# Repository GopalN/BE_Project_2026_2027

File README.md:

# BE CAPSTONE PROJECT 

## 🤖 Decentralized Swarm Autonomous Ground Vehicles
<p align="left">
  
</p>

---
## 👥 Team Details

| **Sr. No.** | **Name of Student** | **Roll No.** | **Branch** | **Email ID** |
|:---:|:---|:---:|:---|:---|
| 1 | Abbas Najam | 59 |Automation and Robotics | [2023.abbas.najam@ves.ac.in](mailto:2023.abbas.najam@ves.ac.in) |
| 2 | Mayuresh Joshi | 49 | Automation and Robotics | [2023.mayuresh.joshi@ves.ac.in](mailto:2023.mayuresh.joshi@ves.ac.in) |
| 3 | Shravan Umrale | 66 | Automation and Robotics | [2023.shravan.umrale@ves.ac.in](mailto:2023.shravan.umrale@ves.ac.in) |
| 4 | Yash Vaychal | 31 | Automation and Robotics | [2023.yash.vaychal@ves.ac.in](mailto:2023.yash.vaychal@ves.ac.in) |

---

## Guide Details

**Project Guide:**  Deepti Khimani

**Department:** Automation and Robotics  

**Institute:** VESIT, Mumbai

# 📌 Project Overview

Swarm robotics is inspired by the collective behavior observed in nature such as ants, bees, and birds. It involves multiple autonomous robots coordinating with each other to accomplish complex tasks efficiently.

This project focuses on developing a **decentralized swarm of Autonomous Ground Vehicles (AGVs)** capable of collaborative operation without depending on a single central controller.

The proposed system combines autonomous navigation, mapping, localization, swarm intelligence, distributed decision-making, communication, and fault detection and recovery.

The system is designed to operate reliably even when an individual robot experiences a failure.

### Key Capabilities

* 🤖 Autonomous navigation
* 🗺️ Mapping and localization
* 📡 Robot-to-robot communication
* 🧠 Decentralized decision-making
* 🤝 Swarm intelligence
* 🚨 Fault detection
* 🔄 Fault recovery
* 🧭 Path planning
* 🚧 Obstacle avoidance
* 🔀 Task reallocation
* ⚙️ Distributed motion control

---

# 🎯 Problem Statement

Most swarm robotic systems currently exist in a **centralized architecture**, where a central controller is responsible for coordinating the robots.

However, in real-world applications, we cannot rely on a single point of failure. If the central controller fails or communication with it is lost, the entire swarm can be affected.

Therefore, this project aims to develop a **decentralized swarm system with fault detection and recovery mechanisms**, where individual robots can communicate with neighboring robots, make local decisions, detect failures, and continue the mission collectively.

---

# 🚀 Objectives

The major objectives of this project are:

* Develop a decentralized multi-robot swarm system.
* Enable communication between multiple autonomous ground vehicles.
* Implement autonomous navigation.
* Implement mapping and localization.
* Develop obstacle avoidance capabilities.
* Implement distributed decision-making.
* Introduce swarm intelligence algorithms.
* Detect communication, sensor, and motor-related faults.
* Develop fault recovery mechanisms.
* Reallocate tasks when a robot becomes unavailable.
* Maintain swarm operation after individual robot failure.
* Validate the system through simulation.
* Develop and test physical AGV prototypes.
* Evaluate swarm performance under different fault conditions.

---
## Existing System

Describe the currently available system or method.

Mention its limitations:

- High cost
- Low accuracy
- Manual process
- Lack of automation
- Poor scalability
- Limited accessibility

---

## Proposed System

Describe your proposed solution.

Include:

- Main idea
- How it works
- Major components
- Expected benefits

---

## System Architecture

Add block diagram or system architecture image here.

```markdown

````

Briefly explain the architecture.

---

## Hardware Requirements

| Sr. No. | Component | Specification | Quantity | Purpose |
| ------- | --------- | ------------- | -------- | ------- |
| 1       |           |               |          |         |
| 2       |           |               |          |         |
| 3       |           |               |          |         |
| 4       |           |               |          |         |

---

## Software Requirements

| Sr. No. | Software / Tool | Version | Purpose |
| ------- | --------------- | ------- | ------- |
| 1       |                 |         |         |
| 2       |                 |         |         |
| 3       |                 |         |         |

---

## Technologies Used

Mention technologies used in the project.

Example:

* Embedded C / Python / JavaScript
* Arduino / STM32 / ESP32 / Raspberry Pi
* ROS / MATLAB / Simulink
* Machine Learning / Computer Vision
* IoT / Cloud / Mobile App
* PCB Design / CAD Design

---

## Methodology

Explain the step-by-step approach.

1. Literature survey
2. Problem identification
3. Requirement analysis
4. System design
5. Hardware/software development
6. Integration
7. Testing and validation
8. Documentation and publication

---

## Project Timeline

| Week / Month | Task Planned          | Status                            |
| ------------ | --------------------- | --------------------------------- |
| Week 1       | Problem finalization  | Pending / In Progress / Completed |
| Week 2       | Literature survey     |                                   |
| Week 3       | Requirement analysis  |                                   |
| Week 4       | System design         |                                   |
| Week 5       | Prototype development |                                   |
| Week 6       | Testing               |                                   |
| Week 7       | Documentation         |                                   |
| Week 8       | Paper writing         |                                   |

---

## Weekly Progress Updates

Students must update this section every week.

| Week   | Date | Work Completed | Work Planned for Next Week | Issues / Challenges | GitHub Commit Link |
| ------ | ---- | -------------- | -------------------------- | ------------------- | ------------------ |
| Week 1 |      |                |                            |                     |                    |
| Week 2 |      |                |                            |                     |                    |
| Week 3 |      |                |                            |                     |                    |
| Week 4 |      |                |                            |                     |                    |
| Week 5 |      |                |                            |                     |                    |
| Week 6 |      |                |                            |                     |                    |
| Week 7 |      |                |                            |                     |                    |
| Week 8 |      |                |                            |                     |                    |

---

## Design Files

Upload and link all design files here.

| File Type       | File Name / Link | Description |
| --------------- | ---------------- | ----------- |
| CAD Model       |                  |             |
| Circuit Diagram |                  |             |
| PCB Design      |                  |             |
| Flowchart       |                  |             |
| Simulation File |                  |             |

---

## Circuit Diagram

Add circuit diagram image here.

```markdown

```

---

## Flowchart / Algorithm

Add flowchart image here.

```markdown

```

### Algorithm

1. Start
2. Initialize the system
3. Read input from sensors/user
4. Process the data
5. Generate output/control action
6. Display/store/transmit result
7. Stop

---

## Implementation Details

Explain the actual implementation of the project.

### Hardware Implementation

Write details about connections, components, power supply, sensors, actuators, PCB, enclosure, etc.

### Software Implementation

Write details about code structure, libraries used, algorithms, communication protocols, database, app, cloud, etc.

---

## Code Structure

```text
BE-Capstone-Project/
│
├── README.md
├── docs/
│   ├── literature_survey.md
│   ├── project_report.pdf
│   └── presentation.pptx
│
├── hardware/
│   ├── circuit_diagram.png
│   ├── pcb_design/
│   └── cad_model/
│
├── software/
│   ├── src/
│   ├── include/
│   └── tests/
│
├── images/
│   ├── system_architecture.png
│   ├── prototype_photo.jpg
│   └── results.png
│
└── references/
    └── papers/
```

---

## How to Run the Project

### Step 1: Clone the Repository

```bash
git clone https://github.com/username/project-name.git
```

### Step 2: Install Dependencies

```bash
pip install -r requirements.txt
```

or mention specific software/library installation steps.

### Step 3: Upload / Run the Code

```bash
python main.py
```

or

```bash
arduino-cli upload -p COMx --fqbn board_name
```

### Step 4: Observe the Output

Mention the expected output of the project.

---

## Testing and Results

| Test No. | Test Description | Expected Result | Actual Result | Status      |
| -------- | ---------------- | --------------- | ------------- | ----------- |
| 1        |                  |                 |               | Pass / Fail |
| 2        |                  |                 |               | Pass / Fail |
| 3        |                  |                 |               | Pass / Fail |

---

## Result Images / Videos

Add images or videos of the working prototype.

```markdown

```

Video Link: https://youtu.be/-i1T_cCoHbY

```markdown
[Project Demo Video](https://drive.google.com/your-video-link)
```

---

## Applications

Mention real-world applications of the project.

1.
2.
3.
4.

---

## Advantages

1.
2.
3.
4.

---

## Limitations

1.
2.
3.
4.

---

## Future Scope

Mention possible improvements.

1.
2.
3.
4.

---

## Research Paper / Publication

| Item                      | Details                                                   |
| ------------------------- | --------------------------------------------------------- |
| Paper Title               |                                                           |
| Conference / Journal Name |                                                           |
| Paper Status              | Not Started / Drafting / Submitted / Accepted / Published |
| Submission Date           |                                                           |
| Paper Link                |                                                           |

---

## References

Add references in IEEE format.

Example:

```text
[1] A. Author, B. Author, "Title of the Paper," Journal/Conference Name, vol. X, no. Y, pp. xx-yy, Year.
[2] Datasheet / Website / Book reference.
```

---

## Repository Update Guidelines

Each student team must update the GitHub repository regularly.

Minimum expected updates:

* Update README every week.
* Push code changes regularly.
* Upload circuit diagrams, CAD files, PCB files, reports and presentations.
* Add weekly progress in the progress table.
* Maintain proper folder structure.
* Do not upload unnecessary temporary files.
* Each major update should have a meaningful commit message.

Example commit messages:

```text
Added problem statement and objectives
Updated system architecture diagram
Added sensor interfacing code
Updated weekly progress for Week 3
Added testing results and prototype images
```

---

## Declaration

We declare that this project work is carried out by our team as part of the BE Capstone Project. The work will be regularly updated on GitHub and all references used will be properly cited.

---

## License

This project is for academic use only.

Optional:

```text
MIT License / Creative Commons / Institute Use Only
```

```
```

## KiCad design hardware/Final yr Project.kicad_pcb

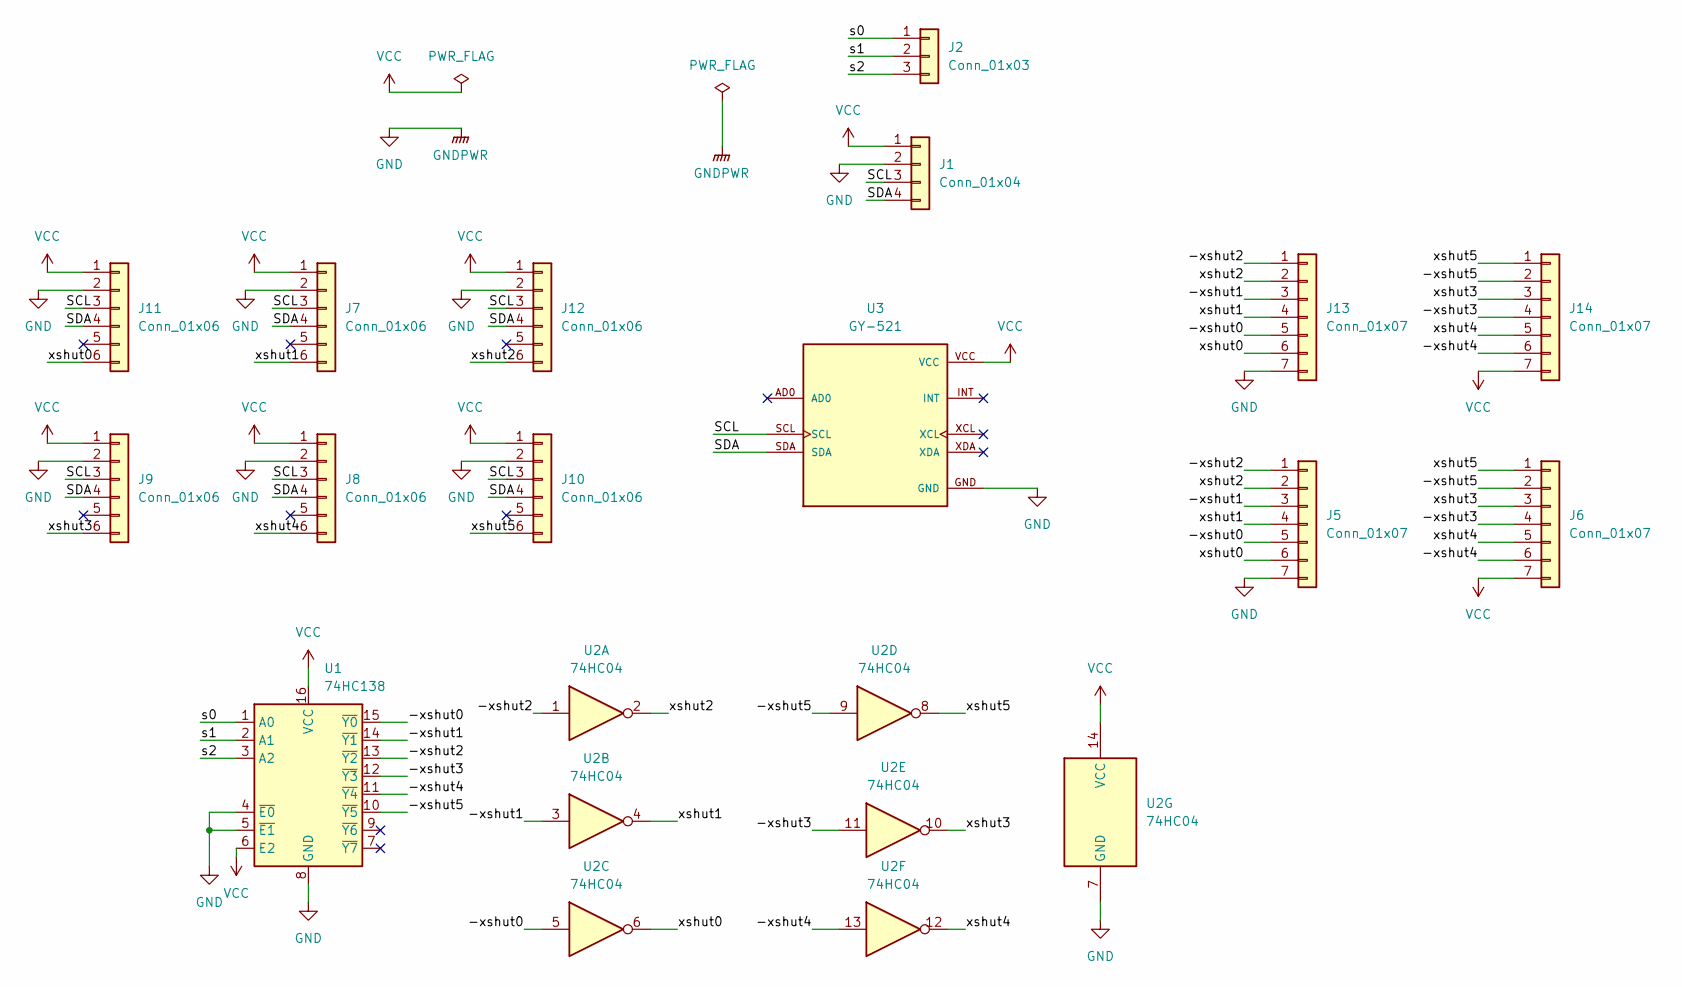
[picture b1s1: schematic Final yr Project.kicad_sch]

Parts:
J1: Conn_01x04; JST_XH_B4B-XH-A_1x04_P2.50mm_Vertical
J2: Conn_01x03; JST_XH_B3B-XH-A_1x03_P2.50mm_Vertical
J5, J6, J13, J14: Conn_01x07; PinHeader_1x07_P2.54mm_Vertical
J7, J8, J9, J10, J11, J12: Conn_01x06; JST_XH_B6B-XH-A_1x06_P2.50mm_Vertical
U1: 74HC138; DIP-16_W7.62mm
U2: 74HC04; DIP-14_W7.62mm
U3: GY-521; MODULE_GY-521; PARTREV NA

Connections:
/-xshut0: J5.5, J13.5, U1.15 (~Y0), U2.5
/-xshut1: J5.3, J13.3, U1.14 (~Y1), U2.3
/-xshut2: J5.1, J13.1, U1.13 (~Y2), U2.1
/-xshut3: J6.4, J14.4, U1.12 (~Y3), U2.11
/-xshut4: J6.6, J14.6, U1.11 (~Y4), U2.13
/-xshut5: J6.2, J14.2, U1.10 (~Y5), U2.9
/SCL: J1.3, J7.3, J8.3, J9.3, J10.3, J11.3, J12.3, U3.SCL
/SDA: J1.4, J7.4, J8.4, J9.4, J10.4, J11.4, J12.4, U3.SDA
/s0: J2.1, U1.1 (A0)
/s1: J2.2, U1.2 (A1)
/s2: J2.3, U1.3 (A2)
/xshut0: J5.6, J11.6, J13.6, U2.6
/xshut1: J5.4, J7.6, J13.4, U2.4
/xshut2: J5.2, J12.6, J13.2, U2.2
/xshut3: J6.3, J9.6, J14.3, U2.10
/xshut4: J6.5, J8.6, J14.5, U2.12
/xshut5: J6.1, J10.6, J14.1, U2.8
GND: J1.2, J5.7, J7.2, J8.2, J9.2, J10.2, J11.2, J12.2, J13.7, U1.4 (~E0), U1.5 (~E1), U1.8 (GND), U2.7 (GND), U3.GND
VCC: J1.1, J6.7, J7.1, J8.1, J9.1, J10.1, J11.1, J12.1, J14.7, U1.6 (E2), U1.16 (VCC), U2.14 (VCC), U3.VCC

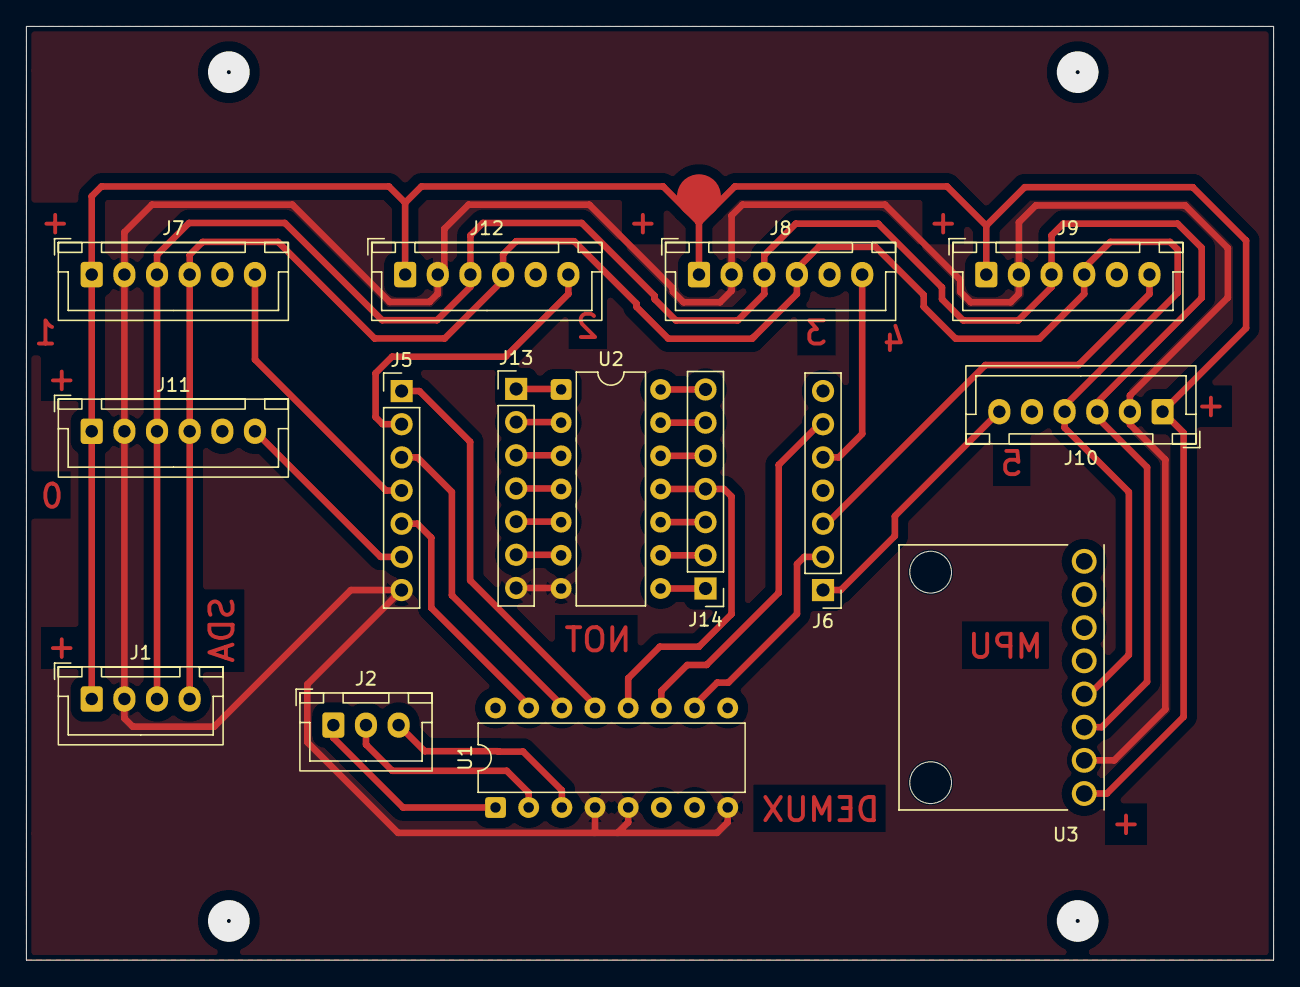
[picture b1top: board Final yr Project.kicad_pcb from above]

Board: 2 copper layers, 95.5 x 71.5 mm, 15 parts (0 on the bottom side), 19 nets.
